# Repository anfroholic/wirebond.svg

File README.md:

<p align="center">
  <picture>
    <source media="(prefers-color-scheme: dark)" srcset="app/brand/wirebond-logo.svg">
    
  </picture>
</p>

<p align="center"><b>A viewable wire bond exchange format, and a browser app that lays out wire bonds for KiCad.</b></p>

<h3 align="center">
  <a href="https://anfroholic.github.io/wirebond.svg/app/">▶&nbsp;Open Wire Bond Bench</a>
</h3>

<p align="center">Runs in your browser. Nothing to install, and your files stay on your computer.</p>

<p align="center">
  <a href="https://anfroholic.github.io/wirebond.svg/examples/example.wb.svg">See an example .wb.svg</a> ·
  <a href="https://anfroholic.github.io/wirebond.svg/docs/primer/wire-bonding-primer.html">Wire bonding primer</a> ·
  <a href="SPEC.md">Spec</a> ·
  <a href="examples">Examples</a> ·
  <a href="tools">Tools</a>
</p>

wirebond.svg is a restricted SVG profile for describing a wire bonded assembly. A `.wb.svg` file opens in any browser as a true-scale bonding diagram, and tools read the same file as data.

> **Status: prototype, v0.2 draft.** Nothing here has been run through a real bonder or offline programming tool.

<table>
  <tr>
    <td width="50%"></td>
    <td width="50%"></td>
  </tr>
  <tr>
    <td></td>
    <td></td>
  </tr>
</table>

## Wire Bond Bench

Wire Bond Bench is the browser app that goes with the format: wire bond layout for KiCad. Give it a die's GDS and the footprint or board it bonds to. It lays out the wires, checks them against bonding design rules, and writes the assembly back to KiCad with 3D wires, a bondlist and a `.wb.svg` bond diagram.

**[Open it in your browser](https://anfroholic.github.io/wirebond.svg/app/)**, in Chrome or Edge. There's nothing to install, and your files stay in the browser. To run it from a copy of this repo instead, open [app/index.html](app/index.html). It is JavaScript only: it never downloads anything or runs Python, so it works offline.

The app opens each of the boards below from its welcome screen. Each picture is the board as the app exports it to KiCad, with the die's artwork painted on from its GDS and every wire in 3D, rendered in Blender.

<table>
  <tr>
    <td colspan="2"></td>
  </tr>
  <tr>
    <td width="50%"></td>
    <td width="50%"></td>
  </tr>
  <tr>
    <td colspan="2"><b>wafer.space die on a real COB board.</b> The logo die on wafer.space's run-2 1x1 <a href="https://github.com/wafer-space/chip-on-board-wire-bonded-pcbs">chip-on-board mezzanine</a>, 74 wires, one per pad.</td>
  </tr>
</table>

| | |
|---|---|
|  |  |
| **The main example.** The logo die on its padring alone: the board in [examples/kicad](examples/kicad), and [examples/example.wb.svg](examples/example.wb.svg). | **EuroSynth.** A synth chip in the 1x0p5 slot, 72 pads, on its padring. |
|  |  |
| **Two die.** The logo die beside a made-up RAM die, wired straight across: [examples/two_die](examples/two_die). | **Stacked die.** The RAM die glued on top of the logo die: [examples/stacked_die](examples/stacked_die). |
|  |  |

## The format

That picture is [examples/example.wb.svg](examples/example.wb.svg), opened in a browser. It is also the data:

- The picture is the data: 1 SVG unit = 1 µm, `stroke-width` is wire diameter, `rect` is a pad opening.
- Height lives in a drawn section view, where a rectangle's height is that layer's thickness.
- Everything else sits on drawn elements as `wb:` attributes.
- Loop shapes are parametric, so one profile fits any wire span.
- Wires reference pads by name, and a checker catches geometry that has drifted.
- The die's artwork is a picture drawn over its outline. It's decoration, and nothing reads data from it.

### What's inside

This is [examples/example.wb.svg](examples/example.wb.svg), cut down to one of each thing. The `<!-- -->` notes are added, and the hover titles, Inkscape layer names and most of the drawing are left out, but the values are the file's own.

```xml
<svg xmlns="http://www.w3.org/2000/svg" xmlns:wb="urn:wbsvg:0.2" viewBox="-300 -500 19000 15600"
     wb:version="0.2" wb:units="um" wb:design="wafer.space 1x1 logo die" wb:rev="A"
     wb:rule-wire-gap="60" wb:rule-edge-clear="40">

  <!-- The board: an outline, and a land per bond finger. 1 unit = 1 µm, so this land is 250 × 1000 µm. -->
  <g>
    <rect x="0" y="0" width="13000" height="13000" class="sub" wb:kind="outline" wb:name="SUB"/>
    <rect x="3175" y="10700" width="250" height="1000" class="cu"
          wb:kind="land" wb:name="L1" wb:net="clk_PAD" wb:finish="ENIG"/>
    <circle cx="900" cy="12100" r="250" class="cu" wb:kind="fiducial" wb:name="F1" wb:role="align" wb:datum="B"/>
  </g>

  <!-- The die, placed by its transform. Inside it, coordinates are the die's own, y up as in its GDS. -->
  <g transform="translate(4534 9061) scale(1 -1)" wb:kind="die" wb:name="U1" wb:gds-cell="chip_top" wb:pad-layer="37/0">
    <rect x="0" y="0" width="3932" height="5122" class="die" wb:kind="outline"/>
    <g transform="scale(1 -1)"><title>U1 artwork</title>
      <image x="0" y="-5122" width="3932" height="5122" href="data:image/png;base64,iVBORw0KGgo…"/>
    </g>
    <rect x="496" y="28" width="60" height="60" class="pad" wb:kind="pad" wb:name="1" wb:net="clk_PAD"/>
  </g>

  <!-- A wire from die pad U1.1 to land L1. stroke-width is the wire's diameter: 20 µm. -->
  <line x1="5060" y1="9003" x2="3300" y2="11000" stroke-width="20" class="w sig"
        wb:kind="wire" wb:name="W01" wb:from="U1.1" wb:to="L1" wb:profile="STD20"
        wb:seq="1" wb:tier="1" wb:net="clk_PAD"/>

  <!-- How the wire loops: a parametric profile that fits any span, drawn beside the plan. -->
  <g wb:kind="profile" wb:name="STD20" wb:material="Au" wb:style="ball-wedge" wb:dir="forward"
     wb:moves="180/0 30/12% -20/35%" wb:interp="spline" wb:ref-span="1000">…</g>

  <!-- Heights: the section view. Each rectangle's height is that layer's thickness: a 280 µm die. -->
  <rect x="4534" y="-305" width="3932" height="280" wb:kind="layer" wb:name="U1" wb:role="die" wb:material="Si"/>

  <!-- Where the die may land: a position tolerance to datums A, B and C. -->
  <g wb:kind="tolerance" wb:applies-to="U1" wb:char="position" wb:tol="50" wb:modifier="CZ" wb:datums="A B C">…</g>
</svg>
```

A reader looks only at elements with a `wb:kind`, and takes their position and size from the drawing itself. Everything else, like the labels, the key and the artwork, is there for people. So the file a browser draws and the file a tool reads can't disagree.

[SPEC.md](SPEC.md) is the format. [docs/report.md](docs/report.md) has the design reasoning and a survey of prior art.

## Examples

Open any `.wb.svg` in [examples/](examples) in a browser and hover over a wire, pad or layer.

| Example | What it is |
|---|---|
| [example.wb.svg](examples/example.wb.svg) | The wafer.space logo die, [89Mods/ws-logo-die](https://github.com/89Mods/ws-logo-die), bonded to the padring of wafer.space's run-2 1x1 [chip-on-board board](https://github.com/wafer-space/chip-on-board-wire-bonded-pcbs). Its pads, net names, eye points and artwork come from the die's GDS, and its lands from the padring footprint. The wire types, stack, board fiducials and tolerance are illustrative. Beside it are the bondlist, fiducials and 3D DXF that `drc.py export` writes from it |
| [waferspace/](examples/waferspace) | The sources: the logo die and EuroSynth as GDS, their padrings, and the run-2 1x1 COB mezzanine board as a KiCad project |
| [two_die/](examples/two_die) | The logo die beside a made-up RAM die on one board, with wires straight across from die to die |
| [stacked_die/](examples/stacked_die) | The RAM die, turned round, glued on top of the logo die |
| [kicad/](examples/kicad) | The first example as a KiCad board |

## Tools

A `.wb.svg` is data, so you can read it from your own code. The `wbsvg` Python package reads one into objects you can query: the bond list, nets, loop profiles, wire lengths, and design rule checks. Its other name is `wirebond`: `pip install wirebond` and `import wirebond` give you the same package.

```sh
pip install wbsvg
wbsvg info examples/example.wb.svg
wbsvg bondlist examples/example.wb.svg -o bonds.csv      # one row per wire, for a bonder
wbsvg query examples/example.wb.svg wire net=VSS         # wires whose wb:net is VSS
wbsvg check examples/example.wb.svg
```

```python
import wbsvg
a = wbsvg.load("examples/two_die/two_die.wb.svg")
a.wire("W75").length              # um, along its loop
a.query("wire", to_kind="die")    # the die-to-die wires
a.net("VSS").pads                 # every pad on VSS
```

[tools/](tools) holds the same Python as single files, `wbsvg.py` and `drc.py`, that you can copy out and run without installing. [tools/README.md](tools/README.md) has the whole API. `drc.py` is the reference checker the app runs: `check`, `place` (how far the die can move before a check fails) and `export` (bondlist, fiducials and 3D DXF). It reads one die, not turned. `wbsvg` reads every example, and runs `drc.py`'s design rules where `drc.py` can read the file.

## Learning

New to wire bonding? These are web pages:

- [The wire bonding primer](https://anfroholic.github.io/wirebond.svg/docs/primer/wire-bonding-primer.html): what bonding is, the words for it, and why each design rule is what it is. The rules are also drawn on [one sheet](https://anfroholic.github.io/wirebond.svg/docs/wire_bond_design_rules.svg).
- [Fiducials](https://anfroholic.github.io/wirebond.svg/docs/primer/fiducials.html): how pick and place machines and wire bonders find the board and the die, and how wirebond.svg describes fiducials.
- [Files in and out](https://anfroholic.github.io/wirebond.svg/docs/primer/files-in-and-out.html): every file the app and `drc.py` read and write, and what round-trips.
- [GD&T](https://anfroholic.github.io/wirebond.svg/docs/primer/gdt.html): the tolerance box beside the die, and the die placement tolerance.

## Handling files

Do not run `.wb.svg` files through SVGO or other minifiers. They convert shapes to paths and remove `id` values, which breaks parsing. Editing in Inkscape, Illustrator or Figma is untested.

## Related work

[open.cob.json](https://github.com/MaxClerkwell/open.cob.json) is a JSON exchange format for chip-on-board wire bonding.

## License

MIT, in [LICENSE](LICENSE). The wafer.space die and board files in [examples/waferspace](examples/waferspace) are Apache-2.0, from the sources in its [SOURCES.md](examples/waferspace/SOURCES.md).

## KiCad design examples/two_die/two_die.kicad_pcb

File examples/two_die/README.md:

# Two die: the logo die beside a RAM die

The wafer.space logo die and a RAM die side by side on one board. Twelve wires go straight across from one die to the other, and the RAM has its own lands to the board for power. It shows what a board with several die looks like, and what wirebond.svg and the Wire Bond Bench can and can't say about one yet.

To see it, open the Wire Bond Bench (`app/index.html`) and choose **wafer.space die beside a RAM die** under Examples. Or open [`two_die.wb.svg`](two_die.wb.svg) in a browser and hover any wire, pad or land.

**What's made up:** the RAM die, its pin order, the board, the wire types and the die thicknesses. The logo die and the padring lands it keeps are the real ones from [`../waferspace`](../waferspace). Nothing here has been bonded.

## The parts

| | |
|---|---|
| D1, the logo die | 3.93 × 5.12 mm, 74 pads, 280 µm thick, where the 1x1 padring puts it |
| D2, the RAM die | 2.2 × 3.0 mm, 25 pads of 70 µm, 200 µm thick, 1.75 mm to the right of D1. A 64 Mbit pseudo-static RAM with a HyperRAM-like bus: eight data lines DQ0 to DQ7, a strobe RWDS, a clock CK, a chip select CS_N and a reset RESET_N. Four memory banks either side of a control strip, drawn in the wafer.space layers so the bench reads it like any other GDS |
| The board | 22 × 16 × 0.8 mm. One bond ring footprint, J1, holds every land for both die and a VSS paddle under each, like the wafer.space padring does for one. Also two global fiducials for pick and place, and four 100 nF decoupling capacitors just outside the glob top. No tracks |

## Where every wire goes

| From | To | Wires | Type |
|---|---|---|---|
| D1's bottom, top and left sides | The padring's lands, pad n to land n | 54 | STD20, PWR20 |
| D1's right edge: VDD and VSS pads 18, 19 and 34 to 37 | Short lands in the gap | 6 | PWR20 |
| D1's pads 26 and 27, VDD and VSS, in the middle of its right edge | Lands 26 and 27 in the gap, shared with the RAM | 2 | PWR20 |
| The RAM's VDD and VSS pads facing D1 | The same lands 26 and 27 | 2 | PWR20 |
| D1's bidir pads on its right edge | The RAM's bus pads, straight across | 12 | D2D20 |
| The RAM's other VDD and VSS pads, on its bottom, right and top | Its own lands, 101 to 110 | 10 | PWR20 |
| The RAM's TEST pad | Nothing: a probe pad for wafer test | 0 | |

86 wires in all. The bus, from the bottom of D1's right edge up:

| D1 pad | D1 net | RAM pin |
|---|---|---|
| 20 to 23 | bidir_PAD[14] to [17] | DQ0 to DQ3 |
| 24 | bidir_PAD[18] | RWDS |
| 25 | bidir_PAD[19] | CK |
| 26, 27 | VDD, VSS | VDD, VSS, through the shared lands |
| 28 | bidir_PAD[20] | CS_N |
| 29 | bidir_PAD[21] | RESET_N |
| 30 to 33 | bidir_PAD[22] to [25] | DQ4 to DQ7 |

## Why it's laid out this way

**The pads face each other at the same pitch.** The RAM's left-edge pads sit at the same heights as D1's right-edge pads, 211 µm apart, so every die-to-die wire runs straight and parallel, and none cross. A real RAM die is bought, and its pads can't move. So in practice you place your own die's bus pads to match the RAM's pin order and pitch. Here the RAM was invented to match D1.

**The gap is set by the lands in it.** The bench's die-edge-to-land rule, from Samtec's die attach guide, asks for 375 µm or twice the die's thickness, whichever is more, because die attach epoxy bleeds out from under the die. That's 560 µm from the 280 µm logo die and 400 µm from the 200 µm RAM. The gap lands are 700 µm long, 600 µm from D1 and 450 µm from the RAM, so the gap is 1.75 mm. The die-to-die wires then span 1.87 mm, which is 93 wire diameters, just under the 100-diameter rule of thumb for wire sag and sweep. With no lands in the gap, the die could sit much closer: Europractice's minimum is 250 µm.

**Power never runs through the other die.** D1 has a VDD and VSS pair in the middle of its right edge, between the bus pads. Each goes to a short land in the gap, and the RAM's own VDD and VSS pads opposite them go to the same lands, one wire from each side, with the two stitches 0.3 mm apart. Every supply pad reaches board copper. On a real board those two lands are boxed in by bus wires, so each would need a via down to an inner plane. D1's other supply pads on that edge sit above and below the RAM and go to their own gap lands.

**The bus wires are ball on D1, stitch on the RAM.** D1 is the higher die, its top at 305 µm against the RAM's 225 µm, so the wire steps down to its stitch as a wire to the board does. A stitch pressed straight onto a die pad can crack the layers under it, so bonders first put a stud bump on each RAM pad, a ball with its wire broken off, and stitch onto that bump. This is called bond stitch on ball (BSOB). The bond order reflects it: the die-to-die wires are bonded last.

**Their loop drops late.** D2D20 rises 150 µm, eases down 60 µm over most of the span, then falls steeply over the last tenth. The RAM's pads are only 60 µm from its edge, and the wire must clear that edge by 40 µm. A loop that came down gradually, like STD20's, would graze it.

**The RAM is thinner.** Memory die are often thinned, and it shows in the section view: two die tops at different heights, with the bus wires stepping down 80 µm.

## What the format and tools can't say yet

- **Nets across two die.** Each die names its pads for itself, so the bench's net check warns on all twelve bus wires: `bidir_PAD[14]` at one end and `DQ0` at the other. The wire's `wb:net` takes the far pad's name, `DQ0`. Neither is the board's net name, such as `RAM_DQ0`, and there's no land to carry one. The format needs a way to give a die-to-die wire its own net and check both pads against it.
- **The stud bumps.** Nothing in the file says the RAM's pads get a bump before their stitch. SPEC.md lists `security-bump` as proposed. This example is a case for it.
- **`drc.py` reads one die.** `drc.py check` can't check this file. It takes the first die and treats every pad as that die's. The bench's own checks cover both die and both ends of every wire.
- **Design rules don't travel in the .wb.svg.** The bench rebuilds a board from the file, but its copper has no nets, and KiCad's default 0.2 mm clearance applies unless you add `two_die.kicad_pro`. For a board to build, assemble from `two_die.kicad_pcb`, as `make_two_die.py` does.

The bench's checks on it: nothing fails. Three things aren't a pass: the twelve net warnings above, D1's 44 long fan-out wires over the 100-diameter rule of thumb (the main example has the same), and the RAM's TEST pad, unbonded on purpose. KiCad's DRC of the assembled board finds nothing but the unrouted nets.

## Files

| File | What it is |
|---|---|
| `make_two_die.py` | Builds everything. The layout's numbers and the wire plan are at its top |
| `psram_die.gds` | The RAM die: outline on 0/0, pads on 37/0, pin names on 81/10, and Metal1 to Metal5 |
| `two_die.kicad_pcb`, `.kicad_pro` | The board as a PCB designer would draw it, before any die or wire. 0.1 mm clearance, as on the wafer.space boards |
| `two_die.wb.svg` | The assembled bond diagram, as the bench writes it: both die with their artwork, every wire, the stack and the board |
| `two_die_3d.png` | The bench's 3D view of it |

## Rebuilding

```sh
pip install gdstk lxml ezdxf playwright
python examples/two_die/make_two_die.py
python app/make_samples.py
```

`make_two_die.py` writes the RAM die and the board, then has the bench put them together in a headless Chrome, since the bench is the only writer that handles several die. It loads the board and both GDS files, puts each die where the plan says, makes every wire, and writes `two_die.wb.svg`. `--inputs` writes only the RAM die and the board. The output is the same byte for byte each time. `tests/test_app.py` runs the same assembly and checks that it still gives this file, and that KiCad passes the assembled board.

The bench's **Put it in KiCad** writes the assembled board with a 3D model of every wire, about 5 MB, so it isn't kept here.

---

<sub> Part of [wirebond.svg](https://github.com/anfroholic/wirebond.svg), a viewable wire bond exchange format, and its browser app Wire Bond Bench. (c) Andrew Wingate, MIT licence.</sub>

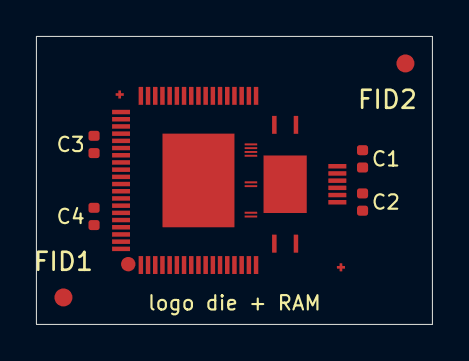
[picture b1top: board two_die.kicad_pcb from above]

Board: 2 copper layers, 22.0 x 16.0 mm, 7 parts (0 on the bottom side), 2 nets, no tracks yet.

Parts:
C1, C2, C3, C4: 100n; C_0402_1005Metric
FID1, FID2: Fiducial; Fiducial_1mm_Mask3mm
J1: two-die bond ring; two_die_bond_ring

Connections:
VDD: C1.1, C2.1, C3.1, C4.1, J1.18 (VDD), J1.26 (VDD), J1.35 (VDD), J1.37 (VDD), J1.58 (VDD), J1.64 (VDD), J1.72 (VDD), J1.74 (VDD), J1.102 (VDD), J1.104 (VDD), J1.106 (VDD), J1.108 (VDD), J1.110 (VDD)
VSS: C1.2, C2.2, C3.2, C4.2, J1.9 (VSS), J1.19 (VSS), J1.27 (VSS), J1.34 (VSS), J1.36 (VSS), J1.46 (VSS), J1.57 (VSS), J1.63 (VSS), J1.71 (VSS), J1.73 (VSS), J1.101 (VSS), J1.103 (VSS), J1.105 (VSS), J1.107 (VSS), J1.109 (VSS), J1.P1 (paddle), J1.P2 (paddle)

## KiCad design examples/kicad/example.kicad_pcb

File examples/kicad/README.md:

# KiCad example

The same assembly as `../example.wb.svg`, the wafer.space logo die on its 1x1 padring, as a KiCad 10 board. It's the input a future KiCad to wirebond.svg importer would read. No importer exists yet. For now `../make_kicad.py` generates these files from the `.wb.svg`, so don't hand-edit them if you plan to regenerate.

KiCad has no bond wire, so this board uses a convention. KiCad preserves that data but doesn't interpret it.

There's no schematic, only `.kicad_pro` and `.kicad_pcb`. Nets exist only as pad assignments, so there's no ERC, and schematic parity checks and Update PCB from Schematic can't be used.

## Units

KiCad mm = SVG µm / 1000, with no offset. Both are y-down. Text values in `wb_` board properties stay in µm, as `wb_units` says.

## Mapping

| wirebond.svg | KiCad object | Where the data is |
|---|---|---|
| Die | Footprint `U1`, anchored at the GDS origin | `(at)` is the translate; `wb_gds_cell`, `wb_pad_layer` |
| Die outline | `fp_rect` on `F.Fab` in `U1` | Width and height |
| Pad | `smd rect` pad on `F.Cu` in `U1` | Number is the GDS pad name; local position is `(gds_x, -gds_y) / 1000`; size is the opening; net |
| Land | One-pad footprint `L1`..`L74`, anchored at the land centre | Pad size and net; `wb_finish` |
| Wire | Padless footprint `W01`..`W74`, anchored at the first bond | One `fp_line` on `Wirebond`, whose end is the second bond and whose width is the diameter; `wb_from`, `wb_to`, `wb_profile`, `wb_seq`, `wb_tier`, `wb_net` |
| Board fiducial | Footprint `F1`, `F2`, `P1`, anchored at the reference point | One unnumbered pad on `F.Cu` and `F.Mask`, mask opened by `wb_rule_fid_clear`; `wb_role`, `wb_datum`. An `align` fiducial's pad has `(property pad_prop_fiducial_glob)`, which KiCad writes into the Gerbers |
| Die fiducial | Not carried | It's die artwork, so it stays with the GDS |
| Substrate outline | `gr_rect` on `Edge.Cuts` | Name in `wb_substrate_name` |
| Design, rev, rules | Board properties | `wb_design`, `wb_rev`, `wb_rule_wire_gap`, `wb_rule_edge_clear`, `wb_rule_fid_clear`, plus `wb_version`, `wb_units` |
| Loop profile | Board properties | `wb_profile_<i>_name`, `_material`, `_d`, `_style`, `_dir`, `_moves`, `_interp`, `_ref_span` |
| Stack layer | Board properties | `wb_stack_<i>_name`, `_role`, `_material`, `_z`, `_t`, `_x`, `_w` |

Each die, land, wire and fiducial footprint has `wb_kind` set to `die`, `land`, `wire` or `fiducial`. A reader should select on that, and ignore other footprints.

The example's fiducials are 500 µm and 300 µm dots, sized for a bonder's camera. Pick and place guides ask for at least 1 mm, so these aren't SMT fiducials.

## For anyone reading the file

- `Wirebond` is a display name. The layer table says `(39 "User.1" user "Wirebond")`, and objects say `(layer "User.1")`. Look the name up in the table.
- KiCad re-sorts footprints and board properties when it saves. Sort wires by `wb_seq`; `<i>` keeps the profile and stack order.
- Apply the footprint's `(at x y angle)` to local coordinates. A rotated wire keeps its original local coordinates.
- A die rotated in KiCad has no equivalent in `drc.rd`, which accepts only a translate and flip.

## Keep the project file

Board properties are repeated in `text_variables` in `example.kicad_pro`, and the two must match. KiCad's `BOARD.SynchronizeProperties()` replaces the board's table with the project's, so an empty project table erases every board property. The generator writes both tables.

To change a board value in the GUI, use Board Setup > Text Variables. The title block shows `${wb_design}` and `${wb_rev}` from the same table.

## What KiCad understands

| KiCad does | KiCad doesn't |
|---|---|
| Keep pad nets, draw the ratsnest, and check copper clearance | Know a wire connects a pad to a land |
| Keep the custom properties and let you edit them | Validate them, or check them against pads and lands |
| Draw and plot wires on `Wirebond` | Run DRC on wires, or apply the wire gap and edge clearance rules |
| Keep the profile and stack values as text | Use them; there are no 3D wires, loops or die heights |

## Expected behaviour

- **DRC:** 0 violations and 90 unconnected items, with the project's 0.1 mm clearance, as on the wafer.space COB boards. The unconnected items are real from KiCad's point of view, because wires aren't copper. Each of the 56 signal nets has one pad and one land, which gives one line. VSS has 10 pads and 10 lands, which gives 19, and VDD 8 and 8, which gives 15.
- **Moving items:** moving `U1` or a land leaves the wires behind, and nothing in KiCad flags it. `wbsvg check` will, once an importer has produced a `.wb.svg`.
- **Gerbers:** die pads are on `F.Cu`, so they plot as substrate copper. Don't send this board's outputs to a fab as they are.

---

<sub> Part of [wirebond.svg](https://github.com/anfroholic/wirebond.svg), a viewable wire bond exchange format, and its browser app Wire Bond Bench. (c) Andrew Wingate, MIT licence.</sub>

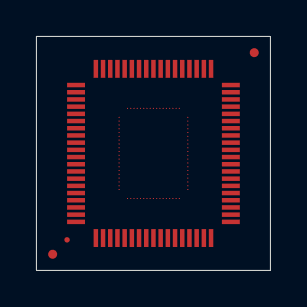
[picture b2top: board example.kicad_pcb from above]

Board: 2 copper layers, 13.0 x 13.0 mm, 152 parts (0 on the bottom side), 58 nets, no tracks yet.

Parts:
F1, F2: fiducial
L1, L2, L3, L4, L5, L6, L7, L8, L9, L10, L11, L12, L13, L14, L15, L16, L17, L18, L19, L20, L21, L22, L23, L24, L25, L26, L27, L28, L29, L30, L31, L32, L33, L34, L35, L36, L37, L38, L39, L40, L41, L42, L43, L44, L45, L46, L47, L48, L49, L50, L51, L52, L53, L54, L55, L56, L57, L58, L59, L60, L61, L62, L63, L64, L65, L66, L67, L68, L69, L70, L71, L72, L73, L74: land
P1: fiducial
U1: chip_top; die
W01, W02, W03, W04, W05, W06, W07, W08, W09, W10, W11, W12, W13, W14, W15, W16, W17, W18, W19, W20, W21, W22, W23, W24, W25, W26, W27, W28, W29, W30, W31, W32, W33, W34, W35, W36, W37, W38, W39, W40, W41, W42, W43, W44, W45, W46, W47, W48, W49, W50, W51, W52, W53, W54, W55, W56, W57, W58, W59, W60, W61, W62, W63, W64, W65, W66, W67, W68, W69, W70, W71, W72, W73, W74: wire

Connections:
VDD: L18.1, L26.1, L35.1, L37.1, L58.1, L64.1, L72.1, L74.1, U1.18, U1.26, U1.35, U1.37, U1.58, U1.64, U1.72, U1.74
VSS: L9.1, L19.1, L27.1, L34.1, L36.1, L46.1, L57.1, L63.1, L71.1, L73.1, U1.9, U1.19, U1.27, U1.34, U1.36, U1.46, U1.57, U1.63, U1.71, U1.73
analog_PAD[0]: L53.1, U1.53
analog_PAD[1]: L54.1, U1.54
bidir_PAD[0]: L3.1, U1.3
bidir_PAD[1]: L4.1, U1.4
bidir_PAD[2]: L5.1, U1.5
bidir_PAD[3]: L6.1, U1.6
bidir_PAD[4]: L7.1, U1.7
bidir_PAD[5]: L8.1, U1.8
bidir_PAD[6]: L10.1, U1.10
bidir_PAD[7]: L11.1, U1.11
bidir_PAD[8]: L12.1, U1.12
bidir_PAD[9]: L13.1, U1.13
bidir_PAD[10]: L14.1, U1.14
bidir_PAD[11]: L15.1, U1.15
bidir_PAD[12]: L16.1, U1.16
bidir_PAD[13]: L17.1, U1.17
bidir_PAD[14]: L20.1, U1.20
bidir_PAD[15]: L21.1, U1.21
bidir_PAD[16]: L22.1, U1.22
bidir_PAD[17]: L23.1, U1.23
bidir_PAD[18]: L24.1, U1.24
bidir_PAD[19]: L25.1, U1.25
bidir_PAD[20]: L28.1, U1.28
bidir_PAD[21]: L29.1, U1.29
bidir_PAD[22]: L30.1, U1.30
bidir_PAD[23]: L31.1, U1.31
bidir_PAD[24]: L32.1, U1.32
bidir_PAD[25]: L33.1, U1.33
bidir_PAD[26]: L38.1, U1.38
bidir_PAD[27]: L39.1, U1.39
bidir_PAD[28]: L40.1, U1.40
bidir_PAD[29]: L41.1, U1.41
bidir_PAD[30]: L42.1, U1.42
bidir_PAD[31]: L43.1, U1.43
bidir_PAD[32]: L44.1, U1.44
bidir_PAD[33]: L45.1, U1.45
bidir_PAD[34]: L47.1, U1.47
bidir_PAD[35]: L48.1, U1.48
bidir_PAD[36]: L49.1, U1.49
bidir_PAD[37]: L50.1, U1.50
bidir_PAD[38]: L51.1, U1.51
bidir_PAD[39]: L52.1, U1.52
clk_PAD: L1.1, U1.1
input_PAD[0]: L55.1, U1.55
input_PAD[1]: L56.1, U1.56
input_PAD[2]: L59.1, U1.59
input_PAD[3]: L60.1, U1.60
input_PAD[4]: L61.1, U1.61
input_PAD[5]: L62.1, U1.62
input_PAD[6]: L65.1, U1.65
input_PAD[7]: L66.1, U1.66
input_PAD[8]: L67.1, U1.67
input_PAD[9]: L68.1, U1.68
input_PAD[10]: L69.1, U1.69
input_PAD[11]: L70.1, U1.70
rst_n_PAD: L2.1, U1.2

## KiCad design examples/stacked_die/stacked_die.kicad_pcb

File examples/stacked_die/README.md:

# Stacked die: a RAM die on top of the logo die

The RAM die from [`../two_die`](../two_die), turned round and glued on top of the wafer.space logo die. Twelve wires step down from the RAM to the logo die's pads, and the RAM's twelve supply wires reach over the logo die to lands on the board. It shows what a stack looks like, and how a board's lands are laid out for one.

To see it, open the Wire Bond Bench (`app/index.html`) and choose **RAM die stacked on the wafer.space die** under Examples. Or open [`stacked_die.wb.svg`](stacked_die.wb.svg) in a browser and hover any wire, pad or land.

**What's made up:** the RAM die and its pin order (the same as the two-die example's), the board, the wire types, the die thicknesses and the attach. The logo die is the real one from [`../waferspace`](../waferspace). Nothing here has been bonded.

## The parts

| | |
|---|---|
| D1, the logo die | 3.93 × 5.12 mm, 74 pads, 280 µm thick, on 25 µm of die attach: its top is 305 µm above the board |
| D2, the RAM die | The two-die example's `psram_die.gds`: 2.2 × 3.0 mm, 25 pads of 70 µm, 200 µm thick. Turned 180° and centred left to right on D1, on 25 µm of attach: its underside is at 330 µm and its top at 530 µm. It covers D1's logo, but none of D1's pads: the nearest bonded pad is 792 µm from its edge |
| The board | 18 × 16 × 0.8 mm. One footprint, J1, holds a single row of 74 lands round D1, the RAM's slotted in among D1's, and a VSS paddle under D1. Also two global fiducials and four 100 nF decoupling capacitors. No tracks |

## Where every wire goes

| From | To | Wires | Type |
|---|---|---|---|
| D1, every pad but the twelve bus pads | Its own land in the row, numbered as the pad | 62 | STD20, PWR20 |
| The RAM's VDD and VSS pads, all twelve | Lands 101 to 112, in the same row, between D1's | 12 | STK23 |
| The RAM's bus pads | D1's bidir pads 20 to 25 and 28 to 33, straight across | 12 | STEP20 |
| The RAM's TEST pad | Nothing: a probe pad for wafer test | 0 | |

86 wires in all. The bus is the two-die example's, with D1's pads on the same nets. Turning the RAM reverses which end is which: D1's pad 33 at the top now takes DQ0, and pad 20 at the bottom DQ7.

| D1 pad | D1 net | RAM pin |
|---|---|---|
| 20 to 23 | bidir_PAD[14] to [17] | DQ7 to DQ4 |
| 24 | bidir_PAD[18] | RESET_N |
| 25 | bidir_PAD[19] | CS_N |
| 26, 27 | VDD, VSS | none: the RAM's VSS and VDD face them, each going on to its own land |
| 28 | bidir_PAD[20] | CK |
| 29 | bidir_PAD[21] | RWDS |
| 30 to 33 | bidir_PAD[22] to [25] | DQ3 to DQ0 |

## Why it's laid out this way

**The RAM is turned 180°.** Its bus is on one long edge, and D1's bidirectional pads are on its right edge. Turned, the RAM's bus edge faces right, and each bus pad sits level with one of D1's, as in the two-die example. So the twelve bus wires run straight and parallel, 868 µm each. A turned die is ordinary in a stack: you can't change a bought die's pads, only how you place it.

**Ball on the RAM, stitch on the logo die.** The RAM is the higher die, so the wire starts there and steps down 225 µm to D1, as a wire to the board steps down from its die. Its stitch lands on an active die pad, so bonders put a stud bump on each of D1's twelve bus pads first and stitch onto that: bond stitch on ball (BSOB), as on the RAM's pads in the two-die example. Those wires are bonded last. Each comes to its pad from over D1, from the inside, which the bench's angle check now allows for (see below).

**One row of lands, close in.** The 1x1 padring's lands are 1.8 mm from the die, which is fine for one die. Here every land's inner end is 565 µm from D1: the die-edge-to-land rule asks for twice the die's 280 µm thickness, because die attach bleeds out from under it. D1's wires are short, 688 to 939 µm, so none passes the 100-diameter rule of thumb, against 44 on the padring. The lands are 100 µm wide and 130 µm long, at a pitch of 205 µm or more, which leaves 105 µm of board between them for the 0.1 mm clearance. D1's pads are 180 µm apart on its short edges and 211 µm on its long ones, so its lands fan out a little: the outermost wire leaves its pad at 43°, under the 45° limit.

**The RAM's supply wires reach over to the same row.** Each goes in a straight line from its pad, over D1's surface, through a gap between two of D1's pads, and onto a land of its own between two of D1's lands. In plan it never crosses another wire. It passes at least 80 µm from the pads either side of its gap, and no two wires come closer than 73 µm, over the 60 µm rule. `make_stacked_die.py` searches for the layout: for each RAM wire it tries the nearest gaps and land positions 5 µm apart, and fits D1's lands round them as straight as the pitch allows.

**Those wires are 23 µm, not 20.** They span 1.56 to 2.14 mm, the longest on the board. At 20 µm the longest would be 107 wire diameters; at 23 µm it's 93, under the rule of thumb for sag and sweep. The RAM's 70 µm pads still take a 23 µm wire, at three diameters. D1's 60 µm pads wouldn't, and D1 has no 23 µm wire.

**Their loop stays high, then comes down late.** STK23 rises 200 µm from the RAM's top to 730 µm, stays near there over D1's edge and over the balls and loops of D1's own wires, and comes down over the last 30% of its span. The bench's die edge check, which follows each wire over every die it passes, finds no wire closer than 137 µm to an edge. The highest loop on the board is 750 µm.

**The lower die is bonded first.** Its wires are the lowest. The RAM's wires to the board come next, higher, passing between them, and the RAM's wires down to D1 go last, after their stud bumps.

**The supply pair in the middle of the bus.** In the two-die example, D1's VDD and VSS pads 26 and 27 shared two lands with the RAM's VDD and VSS opposite them. Turned, the RAM's pair is the wrong way round: its VSS faces D1's VDD, and its VDD faces D1's VSS. So nothing is shared. D1's pads 26 and 27 go straight out to their lands, and the RAM's pair angle away from them by 7.5°, out through the gaps on either side, to lands 103 and 104.

## What the format and tools can't say yet

- **Nets across two die.** As in the two-die example, each die names its pads for itself, so the twelve bus wires warn: `bidir_PAD[14]` at one end and `DQ7` at the other.
- **The stud bumps.** Nothing in the file says D1's bus pads get a bump before their stitch. SPEC.md lists `security-bump` as proposed.
- **`drc.py` reads one die,** and not a turned one, so `drc.py check` can't check this file. The bench's checks cover both die.
- **Loop heights in the wire gap check.** Nothing crosses here, so it doesn't matter, but the bench's 60 µm wire-to-wire gap is measured in plan. A stack that let the RAM's wires cross over D1's, as multi-tier packages do, would warn on every crossing even where the loops are far apart. Its crossing check between different die does compare heights.

The bench's checks on it: nothing fails, nothing crosses, and only the twelve net warnings aren't a pass. It also notes that the RAM's twelve wires to the board run over another die, and that the RAM's TEST pad isn't bonded. KiCad's DRC of the board, and of the assembled board the bench writes, finds nothing but the unrouted nets.

## Two changes to the bench this example needed

- **The angle check, on a lower die.** It measured every wire against the direction straight out from the pad's die edge. A wire coming down from a die stacked above reaches the lower die's pad from inside, so the twelve bus wires read 180°. Now, when a wire's other end is over the same die, the angle is measured from the inward direction, and they read 0°.
- **Courtyards in the KiCad export.** Each die footprint had a courtyard, so the RAM's sat inside the logo die's, and KiCad's DRC reported overlapping courtyards. A die on another die takes no board space of its own, so it's now written without one, marked `allow_missing_courtyard`.

## Files

| File | What it is |
|---|---|
| `make_stacked_die.py` | Builds everything. The layout's numbers are at its top, and `fan()` lays out each side's row |
| `stacked_die.kicad_pcb`, `.kicad_pro` | The board as a PCB designer would draw it, before any die or wire. 0.1 mm clearance |
| `stacked_die.wb.svg` | The assembled bond diagram, as the bench writes it: both die with their artwork, every wire, the stack and the board |
| `stacked_die_3d.png` | The bench's 3D view of it |

The RAM die is `../two_die/psram_die.gds`, read from there, not copied.

## Rebuilding

```sh
pip install gdstk lxml ezdxf playwright
python examples/stacked_die/make_stacked_die.py
python app/make_samples.py
```

`make_stacked_die.py` writes the board, then has the bench put it together in a headless Chrome. It loads the board and both GDS files, puts the logo die on the board and the RAM on the logo die, makes every wire, and writes `stacked_die.wb.svg`. `--inputs` writes only the board. The output is the same byte for byte each time. `tests/test_app.py` runs the same assembly and checks that it still gives this file, and that KiCad passes the assembled board.

---

<sub> Part of [wirebond.svg](https://github.com/anfroholic/wirebond.svg), a viewable wire bond exchange format, and its browser app Wire Bond Bench. (c) Andrew Wingate, MIT licence.</sub>

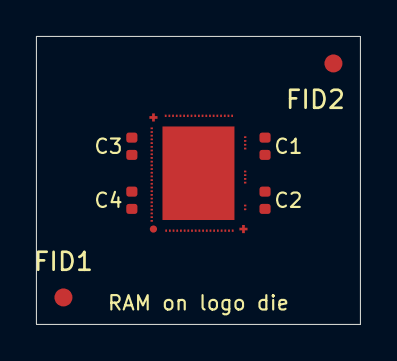
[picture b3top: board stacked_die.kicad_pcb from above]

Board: 2 copper layers, 18.0 x 16.0 mm, 7 parts (0 on the bottom side), 2 nets, no tracks yet.

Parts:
C1, C2, C3, C4: 100n; C_0402_1005Metric
FID1, FID2: Fiducial; Fiducial_1mm_Mask3mm
J1: stacked die bond ring; stacked_die_bond_ring

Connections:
VDD: C1.1, C2.1, C3.1, C4.1, J1.18 (VDD), J1.26 (VDD), J1.35 (VDD), J1.37 (VDD), J1.58 (VDD), J1.64 (VDD), J1.72 (VDD), J1.74 (VDD), J1.102 (VDD), J1.104 (VDD), J1.106 (VDD), J1.108 (VDD), J1.110 (VDD), J1.112 (VDD)
VSS: C1.2, C2.2, C3.2, C4.2, J1.9 (VSS), J1.19 (VSS), J1.27 (VSS), J1.34 (VSS), J1.36 (VSS), J1.46 (VSS), J1.57 (VSS), J1.63 (VSS), J1.71 (VSS), J1.73 (VSS), J1.101 (VSS), J1.103 (VSS), J1.105 (VSS), J1.107 (VSS), J1.109 (VSS), J1.111 (VSS), J1.P1 (paddle)
